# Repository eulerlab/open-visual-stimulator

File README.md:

## Open Visual Stimulator

This repository holds the resources for a flexible, spatial visual stimulator with up to 6 chromatic channels. It combines commercial digital light processing (DLP) devices with open hard- and software components that can be easily adapted to the experimentalist’s specific needs. With this we intend to start a community effort of sharing and further developing a common stimulator design.

Please find more details on the stimulator in the following publication:
  
_Franke K*, Maia Chagas A*, Zhao Z, Zimmermann MJY, Bartel P, Qiu Y, Szatko K, Baden T, Euler T# (2019). An arbitrary-spectrum spatial visual stimulator for vision research. eLife 2019;8:e48779, [10.7554/eLife.48779](https://elifesciences.org/articles/48779)._

For the newest changes and additions, see [release notes](https://github.com/eulerlab/open-visual-stimulator/blob/master/release_notes.md)

### Pictures

_Rendering of the 4-channel R-G-B-UV zebrafish stimulator (by MJY Zimmermann)._

_Rendering of through-the-conderser (TTC) G-UV mouse light stimulator (by MJY Zimmermann)._

_Rendering of through-the-objective (TTO) G-UV mouse light stimulator (by MJY Zimmermann)._ 

### Ordering of PCB boards

If you are interested in ordering boards and components, please find more information in the boards folder [readme](https://github.com/eulerlab/open-visual-stimulator/blob/master/boards/readme.md) file.

## Repository structure

```
├───pics                                      Pictures
├───boards                                    LED driver/blanking boards
│   ├───lcr_add-on                            - KiCad files for board that combines LCr and
|   |   |                                       blanking signals
|   |   ├───connector_coaxial.pretty          - BNC connector description (KiCad)
|   |   └───gerber                            - Gerber files for circuit board
│   ├───mosfet_circuit                        - KiCad files for board that switches switch LEDs
|   |   ├───connector_coaxial.pretty          - BNC connector description (KiCad)
|   |   └───gerber                            - Gerber files for circuit board
|   ├───mosfet_circuit_plus_voltage_regulator - KiCad files for board that combines voltage
|   |   |                                       regulator and LED switching
|   |   ├───connector_coaxial.pretty          - BNC connector description (KiCad)
|   |   └───gerbers                           - Gerber files for circuit board
|   ├───ssr_board                             - KiCad files for solid state relay board
|   |   └───gerbers                           - Gerber files for circuit board
|   └───arduino_code_for_testing_circuits     - Arduino code to emulate blanking and LCr signals
|       └───lcr_emulator
|
├───printed_parts                             OpenSCAD and STL files for 3D printed parts
|   |
│   ├───Fish_cinema                           - Fish tank used in the fish setup
│   ├───SSR_board                             - Designs for plate and cover of the SSR board
│   └───optical_components                    - optomechanical parts for LED assemblies
|           ├───fish_stimulator
|           ├───cmouse_stimulator
|           └───lcr_addons
├───calibration_mouse                         Calibration of dichroic mouse stimulator
│   ├───data                                  - recorded calibration data (custom LEDs and TFT monitor)
│   ├───datasheets                            - spectrometer data sheet, etc.
│   ├───filters                               - dichroic filter spectra
│   ├───light-sources                         - spectra of LEDs
│   ├───opsins                                - mouse opsin sensitivity curves
│   ├───scripts                               - Python scripts used in iPython notebooks
|   └───spectrometer-calibration-files        - USB2+ calibration data
|
└───calibration_zebrafish                     Calibration of tetrachromatic zebrafish stimulator
    ├───data                                  - recorded calibration data (custom LEDs)
    ├───datasheets                            - spectrometer & powermeter data sheet.
    ├───light-sources                         - LED spectra measured behind the teflon screen
    ├───opsins                                - zebrafish opsin sensitivity curves
    └───scripts                               - Python scripts used in iPython notebooks
```

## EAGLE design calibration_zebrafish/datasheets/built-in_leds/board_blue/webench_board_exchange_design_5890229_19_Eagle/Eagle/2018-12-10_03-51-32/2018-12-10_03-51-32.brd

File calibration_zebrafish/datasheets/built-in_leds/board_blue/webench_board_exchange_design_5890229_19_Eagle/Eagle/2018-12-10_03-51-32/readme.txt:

**********************************************************
*************  Important Instructions Follow  ************
**********************************************************
 
All files exported to: Z:\\58\\90\\5890229\\19\Eagle\2018-12-10_03-51-32\2018-12-10_03-51-32.xml

**********************************************************
*****************Schematic Instructions  *******************
**********************************************************

To import your new Schematic file into Eagle:

1. Unzip the downloaded folder files to local directory and Start Eagle.
2. Select "File"->"Open"->"Schematic..." from the menu at the top of
the screen.
3. Browse to your newly exported file and select the ".sch" file extension.
4. You should now see your schamtic available in Eagle.

**********************************************************
*******************  PCB Instructions  *******************
**********************************************************

To import your new BOARD file into Eagle:

1. Unzip the downloaded folder files to local directory and Start Eagle.
2. Select "File"->"Open"->"Board..." from the menu at the top of
the screen.
3. Browse to your newly exported file and select the ".brd" file extension.
4. Planes will need to be repoured to update the polygon fills
	1. Once your board is loaded, type "ratsnest" into the command
	   line and press the Enter key.
	2. The polygons should all be filled now.
5. You should now have an image of your board available in Eagle.

**********************************************************
*******************  LIB Instructions  *******************
**********************************************************

To import your new library into Eagle:

1. Start Eagle.
2. Select "File"->"New"->"Library" from the menu.
3. In the blank library window, select "File" -> "Execute Script"
from the menu.
5. Browse to your newly exported Eagle Script file (".scr" file extension)
6. After opening the file, the script will populate the new library.
Layer 93 should NOT exist.
7. Use "File"->Save As: "AcceleratedDesigns_Lib.lbr" and to the desired
location in Eagle native format.
8. Update schematic with the imported library, Select Library and click on Update; open the library file
	and sync. each part.

For additional information, please visit this site:
http://www.accelerated-designs.com/help/Eagle_import.html

You may also find this video helpful:
http://youtu.be/5jGuWY-Yy3Q

**********************************************************
**********************************************************
**********************************************************

Component "6SVPE220MW" renamed to "6SVPE220MW"
Component "ECPU1C474MA5" renamed to "ECPU1C474MA5"
Component "GRM155R71C104KA88D" renamed to "GRM155R71C104KA88D"
Component "C0805C391J5GACTU" renamed to "C0805C391J5GACTU"
Component "GRM21BR61E475KA12L" renamed to "GRM21BR61E475KA12L"
Component "CRCW080543K2FKEA" renamed to "CRCW080543K2FKEA"
Component "C2012C0G1H153J085AA" renamed to "C2012C0G1H153J085AA"
Component "EMK212BJ225KG-T" renamed to "EMK212BJ225KG-T"
Component "LM3150MH/NOPB" renamed to "LM3150MH/NOPB"
Component "XAL5030-332MEB" renamed to "XAL5030-332MEB"
Component "CSD17307Q5A" renamed to "CSD17307Q5A"
Component "CSD17577Q5A" renamed to "CSD17577Q5A"
Component "CRCW080510K0FKEA" renamed to "CRCW080510K0FKEA"
Component "ERJ-6ENF5112V" renamed to "ERJ-6ENF5112V"
Component "C0805C223K5RACTU" renamed to "C0805C223K5RACTU"
Component "TP-1502" renamed to "TP-1502"

Ultra Librarian Gold 8.1.204 Process Report

Message - Padstack "RX44Y57D0T" Shape(4) is a CIRCLE with no diameter.
Message - Padstack "RX44Y71D0T" Shape(4) is a CIRCLE with no diameter.
Message - Padstack "RX22Y24D0T" Shape(4) is a CIRCLE with no diameter.
Message - Padstack "RX115p5Y31D0T" Shape(4) is a CIRCLE with no diameter.
Message - Padstack "RX46Y183D0T" Shape(4) is a CIRCLE with no diameter.
Message - Padstack "RX31p5Y27p56D0T" Shape(4) is a CIRCLE with no diameter.
Message - Padstack "RX4p3Y4p56D0T" Shape(4) is a CIRCLE with no diameter.
Message - Padstack "RX56Y14D0T" Shape(4) is a CIRCLE with no diameter.
Message - Padstack "RX118Y122D0T" Shape(4) is a CIRCLE with no diameter.
Message - Component "6SVPE220MW" attribute "Datasheet URL" references text style "" that is not in the database.
The default pattern text style "H50s3" was substituted.
Message - Component "6SVPE220MW" attribute "Cap" references text style "" that is not in the database.
The default pattern text style "H50s3" was substituted.
Message - Component "6SVPE220MW" attribute "ESR" references text style "" that is not in the database.
The default pattern text style "H50s3" was substituted.
Message - Component "6SVPE220MW" attribute "IRMS" references text style "" that is not in the database.
The default pattern text style "H50s3" was substituted.
Message - Component "6SVPE220MW" attribute "VDC" references text style "" that is not in the database.
The default pattern text style "H50s3" was substituted.
Message - Component "ECPU1C474MA5" attribute "Datasheet URL" references text style "" that is not in the database.
The default pattern text style "H50s3" was substituted.
Message - Component "ECPU1C474MA5" attribute "Cap" references text style "" that is not in the database.
The default pattern text style "H50s3" was substituted.
Message - Component "ECPU1C474MA5" attribute "ESR" references text style "" that is not in the database.
The default pattern text style "H50s3" was substituted.
Message - Component "ECPU1C474MA5" attribute "IRMS" references text style "" that is not in the database.
The default pattern text style "H50s3" was substituted.
Message - Component "ECPU1C474MA5" attribute "VDC" references text style "" that is not in the database.
The default pattern text style "H50s3" was substituted.
Message - Component "GRM155R71C104KA88D" attribute "Cap" references text style "" that is not in the database.
The default pattern text style "H50s3" was substituted.
Message - Component "GRM155R71C104KA88D" attribute "ESR" references text style "" that is not in the database.
The default pattern text style "H50s3" was substituted.
Message - Component "GRM155R71C104KA88D" attribute "IRMS" references text style "" that is not in the database.
The default pattern text style "H50s3" was substituted.
Message - Component "GRM155R71C104KA88D" attribute "VDC" references text style "" that is not in the database.
The default pattern text style "H50s3" was substituted.
Message - Component "C0805C391J5GACTU" attribute "Cap" references text style "" that is not in the database.
The default pattern text style "H50s3" was substituted.
Message - Component "C0805C391J5GACTU" attribute "ESR" references text style "" that is not in the database.
The default pattern text style "H50s3" was substituted.
Message - Component "C0805C391J5GACTU" attribute "IRMS" references text style "" that is not in the database.
The default pattern text style "H50s3" was substituted.
Message - Component "C0805C391J5GACTU" attribute "VDC" references text style "" that is not in the database.
The default pattern text style "H50s3" was substituted.
Message - Component "GRM21BR61E475KA12L" attribute "Cap" references text style "" that is not in the database.
The default pattern text style "H50s3" was substituted.
Message - Component "GRM21BR61E475KA12L" attribute "ESR" references text style "" that is not in the database.
The default pattern text style "H50s3" was substituted.
Message - Component "GRM21BR61E475KA12L" attribute "IRMS" references text style "" that is not in the database.
The default pattern text style "H50s3" was substituted.
Message - Component "GRM21BR61E475KA12L" attribute "VDC" references text style "" that is not in the database.
The default pattern text style "H50s3" was substituted.
Message - Component "CRCW080543K2FKEA" attribute "Resistance" references text style "" that is not in the database.
The default pattern text style "H50s3" was substituted.
Message - Component "CRCW080543K2FKEA" attribute "Power" references text style "" that is not in the database.
The default pattern text style "H50s3" was substituted.
Message - Component "CRCW080543K2FKEA" attribute "Tolerance" references text style "" that is not in the database.
The default pattern text style "H50s3" was substituted.
Message - Component "C2012C0G1H153J085AA" attribute "Datasheet URL" references text style "" that is not in the database.
The default pattern text style "H50s3" was substituted.
Message - Component "C2012C0G1H153J085AA" attribute "Cap" references text style "" that is not in the database.
The default pattern text style "H50s3" was substituted.
Message - Component "C2012C0G1H153J085AA" attribute "ESR" references text style "" that is not in the database.
The default pattern text style "H50s3" was substituted.
Message - Component "C2012C0G1H153J085AA" attribute "IRMS" references text style "" that is not in the database.
The default pattern text style "H50s3" was substituted.
Message - Component "C2012C0G1H153J085AA" attribute "VDC" references text style "" that is not in the database.
The default pattern text style "H50s3" was substituted.
Message - Component "EMK212BJ225KG-T" attribute "Cap" references text style "" that is not in the database.
The default pattern text style "H50s3" was substituted.
Message - Component "EMK212BJ225KG-T" attribute "ESR" references text style "" that is not in the database.
The default pattern text style "H50s3" was substituted.
Message - Component "EMK212BJ225KG-T" attribute "IRMS" references text style "" that is not in the database.
The default pattern text style "H50s3" was substituted.
Message - Component "EMK212BJ225KG-T" attribute "VDC" references text style "" that is not in the database.
The default pattern text style "H50s3" was substituted.
Message - Component "LM3150MH/NOPB" attribute "Datasheet URL" references text style "" that is not in the database.
The default pattern text style "H50s3" was substituted.
Message - Component "LM3150MH/NOPB" attribute "Frequency" references text style "" that is not in the database.
The default pattern text style "H50s3" was substituted.
Message - Component "LM3150MH/NOPB" attribute "Imax" references text style "" that is not in the database.
The default pattern text style "H50s3" was substituted.
Message - Component "LM3150MH/NOPB" attribute "Package" references text style "" that is not in the database.
The default pattern text style "H50s3" was substituted.
Message - Component "LM3150MH/NOPB" attribute "Mktg_Package" references text style "" that is not in the database.
The default pattern text style "H50s3" was substituted.
Message - Component "LM3150MH/NOPB" attribute "NSID" references text style "" that is not in the database.
The default pattern text style "H50s3" was substituted.
Message - Component "XAL5030-332MEB" attribute "L" references text style "" that is not in the database.
The default pattern text style "H50s3" was substituted.
Message - Component "XAL5030-332MEB" attribute "DCR" references text style "" that is not in the database.
The default pattern text style "H50s3" was substituted.
Message - Component "XAL5030-332MEB" attribute "IDC" references text style "" that is not in the database.
The default pattern text style "H50s3" was substituted.
Message - Component "CSD17577Q5A" attribute "Datasheet URL" references text style "" that is not in the database.
The default pattern text style "H50s3" was substituted.
Message - Component "CSD17577Q5A" attribute "VdsMax" references text style "" that is not in the database.
The default pattern text style "H50s3" was substituted.
Message - Component "CSD17577Q5A" attribute "IdsMax" references text style "" that is not in the database.
The default pattern text style "H50s3" was substituted.
Message - Component "CSD17577Q5A" attribute "Rdsonat10V" references text style "" that is not in the database.
The default pattern text style "H50s3" was substituted.
Message - Component "CSD17577Q5A" attribute "QgTyp" references text style "" that is not in the database.
The default pattern text style "H50s3" was substituted.
Message - Component "CSD17577Q5A" attribute "Quantity" references text style "" that is not in the database.
The default pattern text style "H50s3" was substituted.
Message - Component "CRCW080510K0FKEA" attribute "Resistance" references text style "" that is not in the database.
The default pattern text style "H50s3" was substituted.
Message - Component "CRCW080510K0FKEA" attribute "Power" references text style "" that is not in the database.
The default pattern text style "H50s3" was substituted.
Message - Component "CRCW080510K0FKEA" attribute "Tolerance" references text style "" that is not in the database.
The default pattern text style "H50s3" was substituted.
Message - Component "ERJ-6ENF5112V" attribute "Resistance" references text style "" that is not in the database.
The default pattern text style "H50s3" was substituted.
Message - Component "ERJ-6ENF5112V" attribute "Power" references text style "" that is not in the database.
The default pattern text style "H50s3" was substituted.
Message - Component "ERJ-6ENF5112V" attribute "Tolerance" references text style "" that is not in the database.
The default pattern text style "H50s3" was substituted.
Message - Component "C0805C223K5RACTU" attribute "Cap" references text style "" that is not in the database.
The default pattern text style "H50s3" was substituted.
Message - Component "C0805C223K5RACTU" attribute "ESR" references text style "" that is not in the database.
The default pattern text style "H50s3" was substituted.
Message - Component "C0805C223K5RACTU" attribute "IRMS" references text style "" that is not in the database.
The default pattern text style "H50s3" was substituted.
Message - Component "C0805C223K5RACTU" attribute "VDC" references text style "" that is not in the database.
The default pattern text style "H50s3" was substituted.

TextStyle count:  24
Padstack count:   14
Pattern count:    8
Symbol count:     8
Component count:  16

Export

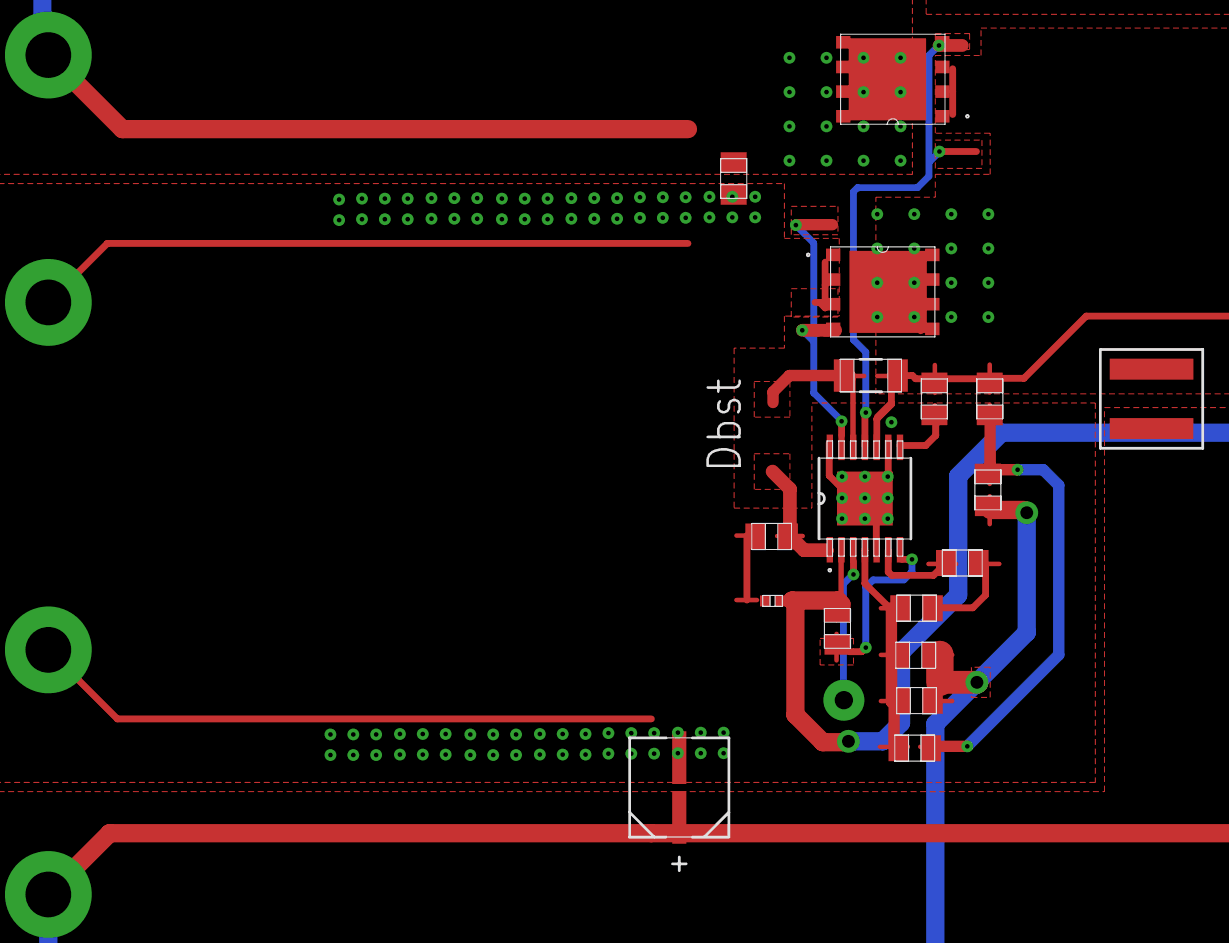
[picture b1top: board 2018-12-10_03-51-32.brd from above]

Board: 4 copper layers, 23 parts (0 on the bottom side), 14 nets.

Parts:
Cac: 0805
Cbst: 1206
Cbyp: 0402
Cff: 0805
Cin: 0805
Cout: CAPSMT_62_E61
Cr: 0805
Css: 0805
Cvcc: 0805
EN: TP-1502
GND, GND1: TP-1502
L1: XAL5030
M1, M2: TRANS_NexFET_Q5A
Rfb1, Rfb2: 0805
Rlim: 0805
Ron: 0805
Rr: 0805
U1: MXA14A
VIN: TP-1502
VOUT: TP-1502

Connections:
0: Cbyp.2, Cin.2, Cout.2, Css.2, Cvcc.2, GND.1, GND1.1, M2.1, M2.2, M2.3, Rfb1.2, U1.5, U1.9, U1.14, U1.15
1: Ron.2, U1.7
2: Cac.1, Cff.2, Rfb1.1, Rfb2.2, U1.4
3: Cbst.2, L1.1, M1.1, M1.2, M1.3, M2.5, M2.6, M2.7, M2.8, M2.9, Rlim.1, Rr.2, U1.10
4: Cbyp.1, Cin.1, M1.5, M1.6, M1.7, M1.8, M1.9, Ron.1, U1.2, VIN.1
5: Cff.1, Cout.1, Cr.2, L1.2, Rfb2.1, VOUT.1
6: Css.1, U1.6
7: M2.4, U1.13
8: Cbst.1, U1.12
9: Cvcc.1, U1.1
10: M1.4, U1.11
11: Rlim.2, U1.8
18: EN.1, U1.3
25: Cac.2, Cr.1, Rr.1

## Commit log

2018-08-08 Consolidate
2018-08-08 Consolidation
2018-08-09 added information about the fish stimulator
2018-08-14 Bug fix (integration time)
2018-08-16 Actual access to spectrometer hardware moved to spectrometer_helper.py
2018-08-21 Update, bug fixes
2018-08-23 Included gamma table
    I included code that: i) fits a sigmoid to the photoisomerisation rate, ii) uses the sigmoid calculate correction curve, iii) exports the gamma table as .txt file
2018-10-05 Updates
    opsin spectrum script updated
2018-12-04 first steps for fish stimulator calibration
    Opsin profiles, first changes in jupyter notebook
2018-12-07 add igor experiment containing opsin traces
2018-12-07 add lcr emulator code for arduino
2018-12-07 add led spec sheets
2018-12-07 new led driver circuit
2018-12-18 update lm3150 design
2018-12-18 testing_import_of_eagle_file
2018-12-18 completed lm3150 pcb
2018-12-19 update to calibration stack
2019-03-06 board folder cleanup
2019-03-06 add voltage and current regulator board, based on lm2596
2019-03-06 rename board to boards
2019-03-06 remove old lm2596 driver
2019-03-06 add back the temp mosfet circuit
2019-03-07 Create Fish Cinema v10.0_40X_Objective.scad
    add modified fish cinema file
2019-03-07 added the led spectra readings where the fish would be
2019-03-10 update LCr board
2019-03-10 clean up add on board
2019-03-10 clean up mosfet circuit
2019-03-11 reorganise led spectra files and add a little code to visualise them
2019-05-08 new board: power supply and sync to led in one
2019-05-09 Updated
    Cleaned up the main folder and data folder. Files that I think we dont need were put into folder "ToDelete". Created Info text file in data folder with details about the example recordings in this fo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
2019-05-09 update calibration stack
2019-05-09 first org
2019-05-09 more org
2019-05-11 added cage components
2019-05-14 added silk information to board
2019-05-15 added revised version of zebrafish calibration notebook and set some files for deletion
2019-05-23 Cleaning up
2019-05-23 zebrafish calibration folder and repo clean up
2019-05-23 created scripts folder for zebrafish calibration
2019-05-23 zipped spectrometer files
2019-05-23 update main readme
2019-05-23 Update spectrometer recording
2019-05-23 Update powermeter recording
2019-05-23 Update Spectrometer Correction Curves
2019-05-24 fixed absolute path issue
2019-07-10 preparing boards for kitspace
2019-07-10 started tracing new board
2019-07-10 added information on how to order boards
2019-07-10 more updates to readme
2019-07-10 final first draft of new board. now to order it and test
2019-07-10 created first draft of BOM
2019-07-11 Fix project names/paths in kitspace.yaml
2019-07-11 Create README.md for lcr_add-on
2019-07-11 Create README.md for mosfet_circuit
2019-07-11 add board renderings
2019-07-11 add another rendering and update kitspace placeholders
2019-07-12 update boms
2019-07-18 new zebrafish calibration folder
2019-07-19 fixed board foot prints
2019-07-19 created 1-click-bom and updated the folder structure
2019-07-19 removed zip from older version of board
2019-07-19 added rendering and readme.md for kitspace
2019-07-29 little board clean up, adding license and date
2019-08-27 adding optocoupler board to repository
2019-08-27 add board rendering
2019-08-27 update 1-click bom optocoupler board
2019-08-27 1-click bom complete
2019-08-28 update readmes and 1-click-bom.csv for solid state relay board
2019-08-28 update readme ssr board
2019-08-28 update kitpsace.yaml to update ssr board
2019-08-29 update 29/08/2019
2019-08-30 Revert "update 29/08/2019"
    This reverts commit 3b09344c82e9eb88c68192b8d4d93b74bff592a6.
2019-08-30 update the calibration zebrafish stuff with Max new data
2019-08-30 update 30/08/2019
2019-08-30 New STL files
2019-08-30 organize printed parts folder
2019-08-30 update readmes
2019-08-30 add DMD lens adapter
2019-09-26 Add picture
2019-10-03 add fibre coupler design
2019-10-03 change readme at base of printed parts folder
2019-10-03 getting local linking right
2019-10-03 add local link to fish stimulator parts and lcr addons
2019-10-04 Illustration pictures update
2019-10-04 illlustration pictures update
2019-10-08 added Ide's contact info and link to the light guide being used (on readme.md in printed parts)
2019-10-11 Picture update
2019-10-23 update the bom.csv file
2019-10-29 created open know how manifest for open visual stimulator
2019-11-05 fix fields in open-visual-stimulator
2019-11-05 correct project link
2019-12-20 Spectral calibration for mouse in vivo experiments
    Added calibration file for mouse in vivo imaging. Includes wavelength-dependent transmission of mouse eye
2020-03-01 update 1-click-boms
2020-03-01 update 1 click boms
2020-03-04 add printed plates to tilt LCr downwards
2020-03-04 split stls
2020-03-05 fine tunning tilt plates
2020-03-06 more fine tunning ggrrrrsskjs
2020-03-10 remove some material to make print faster, add holes for coupling this to mvs005/m from thorlabs
2020-03-11 save maxime
2020-03-12 fixed missing qty for 1-click boms
2020-04-12 add board pictures
2020-04-12 add potentiometer image
2020-10-21 fix side of nut pocket on Lcr tilter design
2021-02-17 final wiring for lcr board
2021-02-17 upload gerbers
2021-02-17 final update
2021-03-17 update board labelling
2021-03-17 update labelling and 1-click-bom
2021-03-17 remove lock file
2021-03-17 update gerbers
2021-08-03 Delete stimulator_calibration.ipynb
    Old version without accounting for pupil size and monitor coverage
2021-08-03 Add updated calibration notebook
    Accounts for
    (i) ratio of pupil area to retinal area
    (ii) spectrometer coverage of monitor
2021-10-10 add mosfet plus voltage regulator link
2021-11-08 Update readme.md
    https://forum.kicad.info/t/warning-avoid-all-links-to-kicad-pcb-org-use-kicad-org/31521
2022-01-26 add initial sketch of ND filter holder
2022-02-14 Various OKH fixes
    * YAML syntax fixes
    * use BCP 47 compliant language identifiers
    * prefer repo-local path over URL to in-repo files
    * use SPDX compliant license identifiers
2022-02-28 update nd filter holder
2022-03-09 update LCR-addon board
    - solve mounting holes
    - solve alignment target on the user layer
    - check connections
2022-03-13 adjust filter holder pocket
2022-05-16 update sock holder
2022-10-13 redesign mosfet circuit board with easier to solder components
2022-10-13 add models for filter holder
2022-10-13 load board with kicad6
2022-10-13 update mosfets on led driver board
2022-11-03 update mosfet id on board
2022-11-03 auto updates and zips
2023-01-14 Add README paths to kitspace.yaml
2023-01-14 Add `eda` to kitspace.yaml
2023-11-18 first prototype of blanking repeater board
2023-12-06 update nd filter holder and remove board backups
